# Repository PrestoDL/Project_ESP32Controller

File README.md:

# Project_ESP32Controller
Project about ESP32 motion controller with ESP-IDF. For IoT properties, additional function will be installed.

Demo test is about controlling light with http request by simple motion.

Demo test in my channel :

https://youtube.com/shorts/M0vYTvH4euw?si=jk3dXooK5vRalX_q

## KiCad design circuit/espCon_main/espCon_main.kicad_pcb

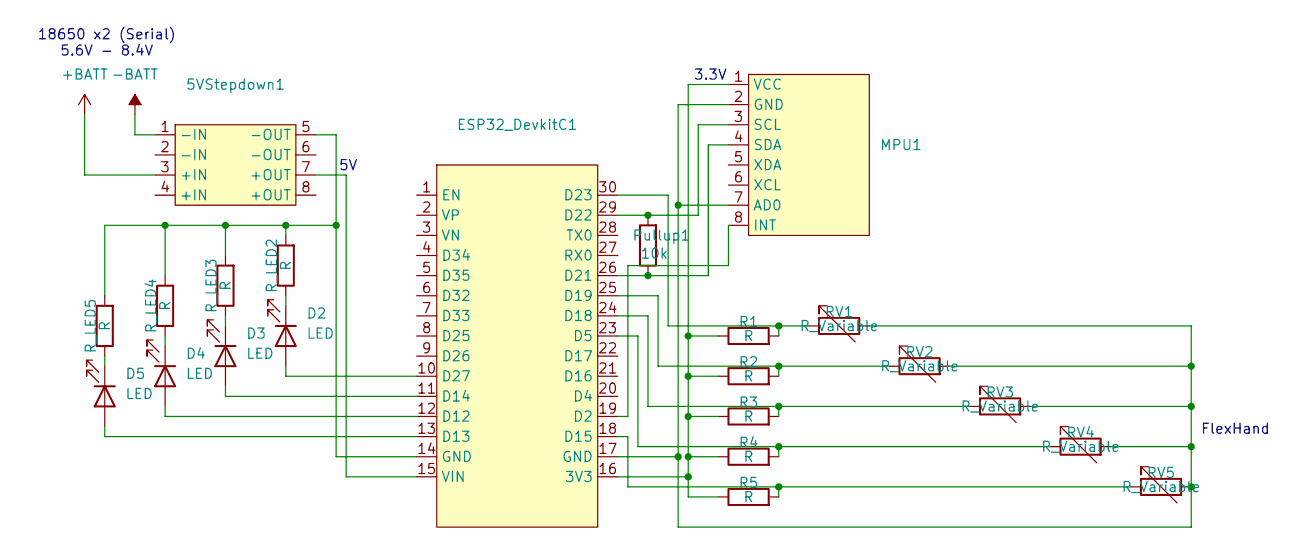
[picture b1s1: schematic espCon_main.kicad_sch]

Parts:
5VStepdown1: 5VStepdown
D2, D3, D4, D5: LED; LED_D1.8mm_W1.8mm_H2.4mm_Horizontal_O1.27mm_Z1.6mm
ESP32_DevkitC1: ESP32_DevkitC
MPU1: GY-521
Pullup1: 10k; R_Axial_DIN0207_L6.3mm_D2.5mm_P2.54mm_Vertical
R1, R2, R3, R4, R5: R; R_Axial_DIN0207_L6.3mm_D2.5mm_P2.54mm_Vertical
RV1, RV2, RV3, RV4, RV5: R_Variable; R_Axial_DIN0207_L6.3mm_D2.5mm_P2.54mm_Vertical
R_LED2, R_LED3, R_LED4, R_LED5: R; R_Axial_DIN0207_L6.3mm_D2.5mm_P2.54mm_Vertical

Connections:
+BATT: 5VStepdown1.3 (+IN)
-BATT: 5VStepdown1.1 (-IN)
unnamed: 5VStepdown1.5 (-OUT), ESP32_DevkitC1.14 (GND), R_LED2.2, R_LED3.2, R_LED4.2, R_LED5.2
unnamed: D2.2 (A), ESP32_DevkitC1.10 (D27)
unnamed: D2.1 (K), R_LED2.1
unnamed: D3.2 (A), ESP32_DevkitC1.11 (D14)
unnamed: D3.1 (K), R_LED3.1
unnamed: D4.2 (A), ESP32_DevkitC1.12 (D12)
unnamed: D4.1 (K), R_LED4.1
unnamed: D5.2 (A), ESP32_DevkitC1.13 (D13)
unnamed: D5.1 (K), R_LED5.1
unnamed: ESP32_DevkitC1.16 (3V3), MPU1.1 (VCC), R1.1, R2.1, R3.1, R4.1, R5.1
unnamed: ESP32_DevkitC1.19 (D2), MPU1.8 (INT)
unnamed: ESP32_DevkitC1.23 (D5), R4.2, RV4.1
unnamed: ESP32_DevkitC1.18 (D15), R5.2, RV5.1
unnamed: ESP32_DevkitC1.24 (D18), R3.2, RV3.1
unnamed: ESP32_DevkitC1.25 (D19), R2.2, RV2.1
unnamed: ESP32_DevkitC1.26 (D21), MPU1.4 (SDA), Pullup1.1
unnamed: ESP32_DevkitC1.29 (D22), MPU1.3 (SCL), Pullup1.2
unnamed: ESP32_DevkitC1.30 (D23), R1.2, RV1.1
unnamed: 5VStepdown1.7 (+OUT), ESP32_DevkitC1.15 (VIN)
unnamed: ESP32_DevkitC1.17 (GND), MPU1.2 (GND), MPU1.7 (AD0), RV1.2, RV2.2, RV3.2, RV4.2, RV5.2

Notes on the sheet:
18650 x2 (Serial) 5.6V - 8.4V
3.3V
FlexHand

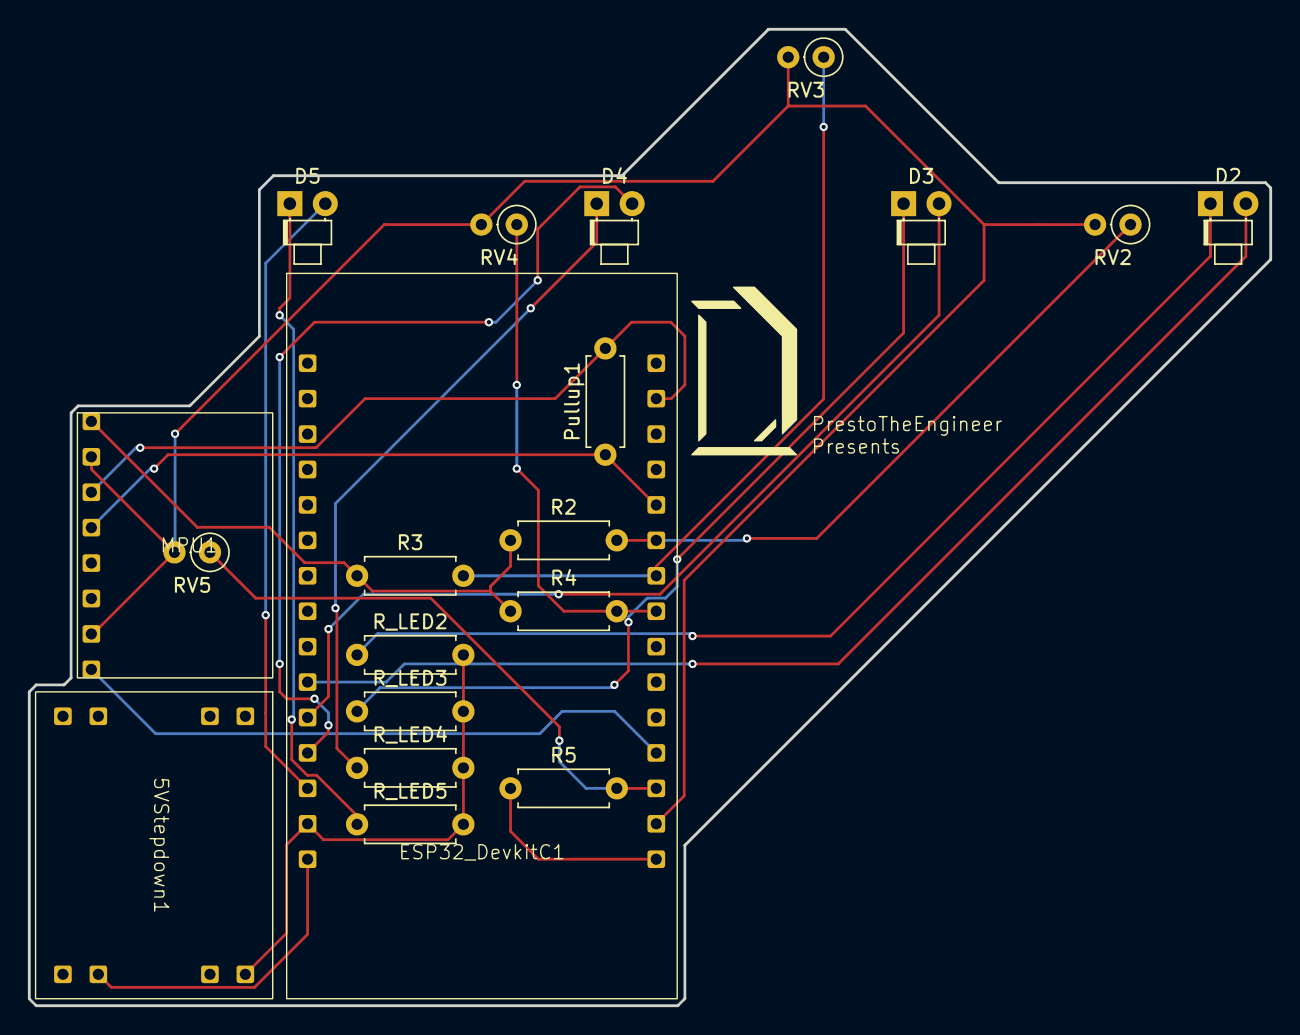
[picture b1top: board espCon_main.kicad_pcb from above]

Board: 2 copper layers, 89.0 x 70.0 mm, 20 parts (0 on the bottom side), 19 nets.

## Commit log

2025-07-20 project init.
2025-08-14 updated controller part with MPU6050
2025-08-25 Update README.md
    added my shorts video
2025-08-26 Update README.md
    uploaded prototype
2025-09-05 Added circuit file and modeling file
